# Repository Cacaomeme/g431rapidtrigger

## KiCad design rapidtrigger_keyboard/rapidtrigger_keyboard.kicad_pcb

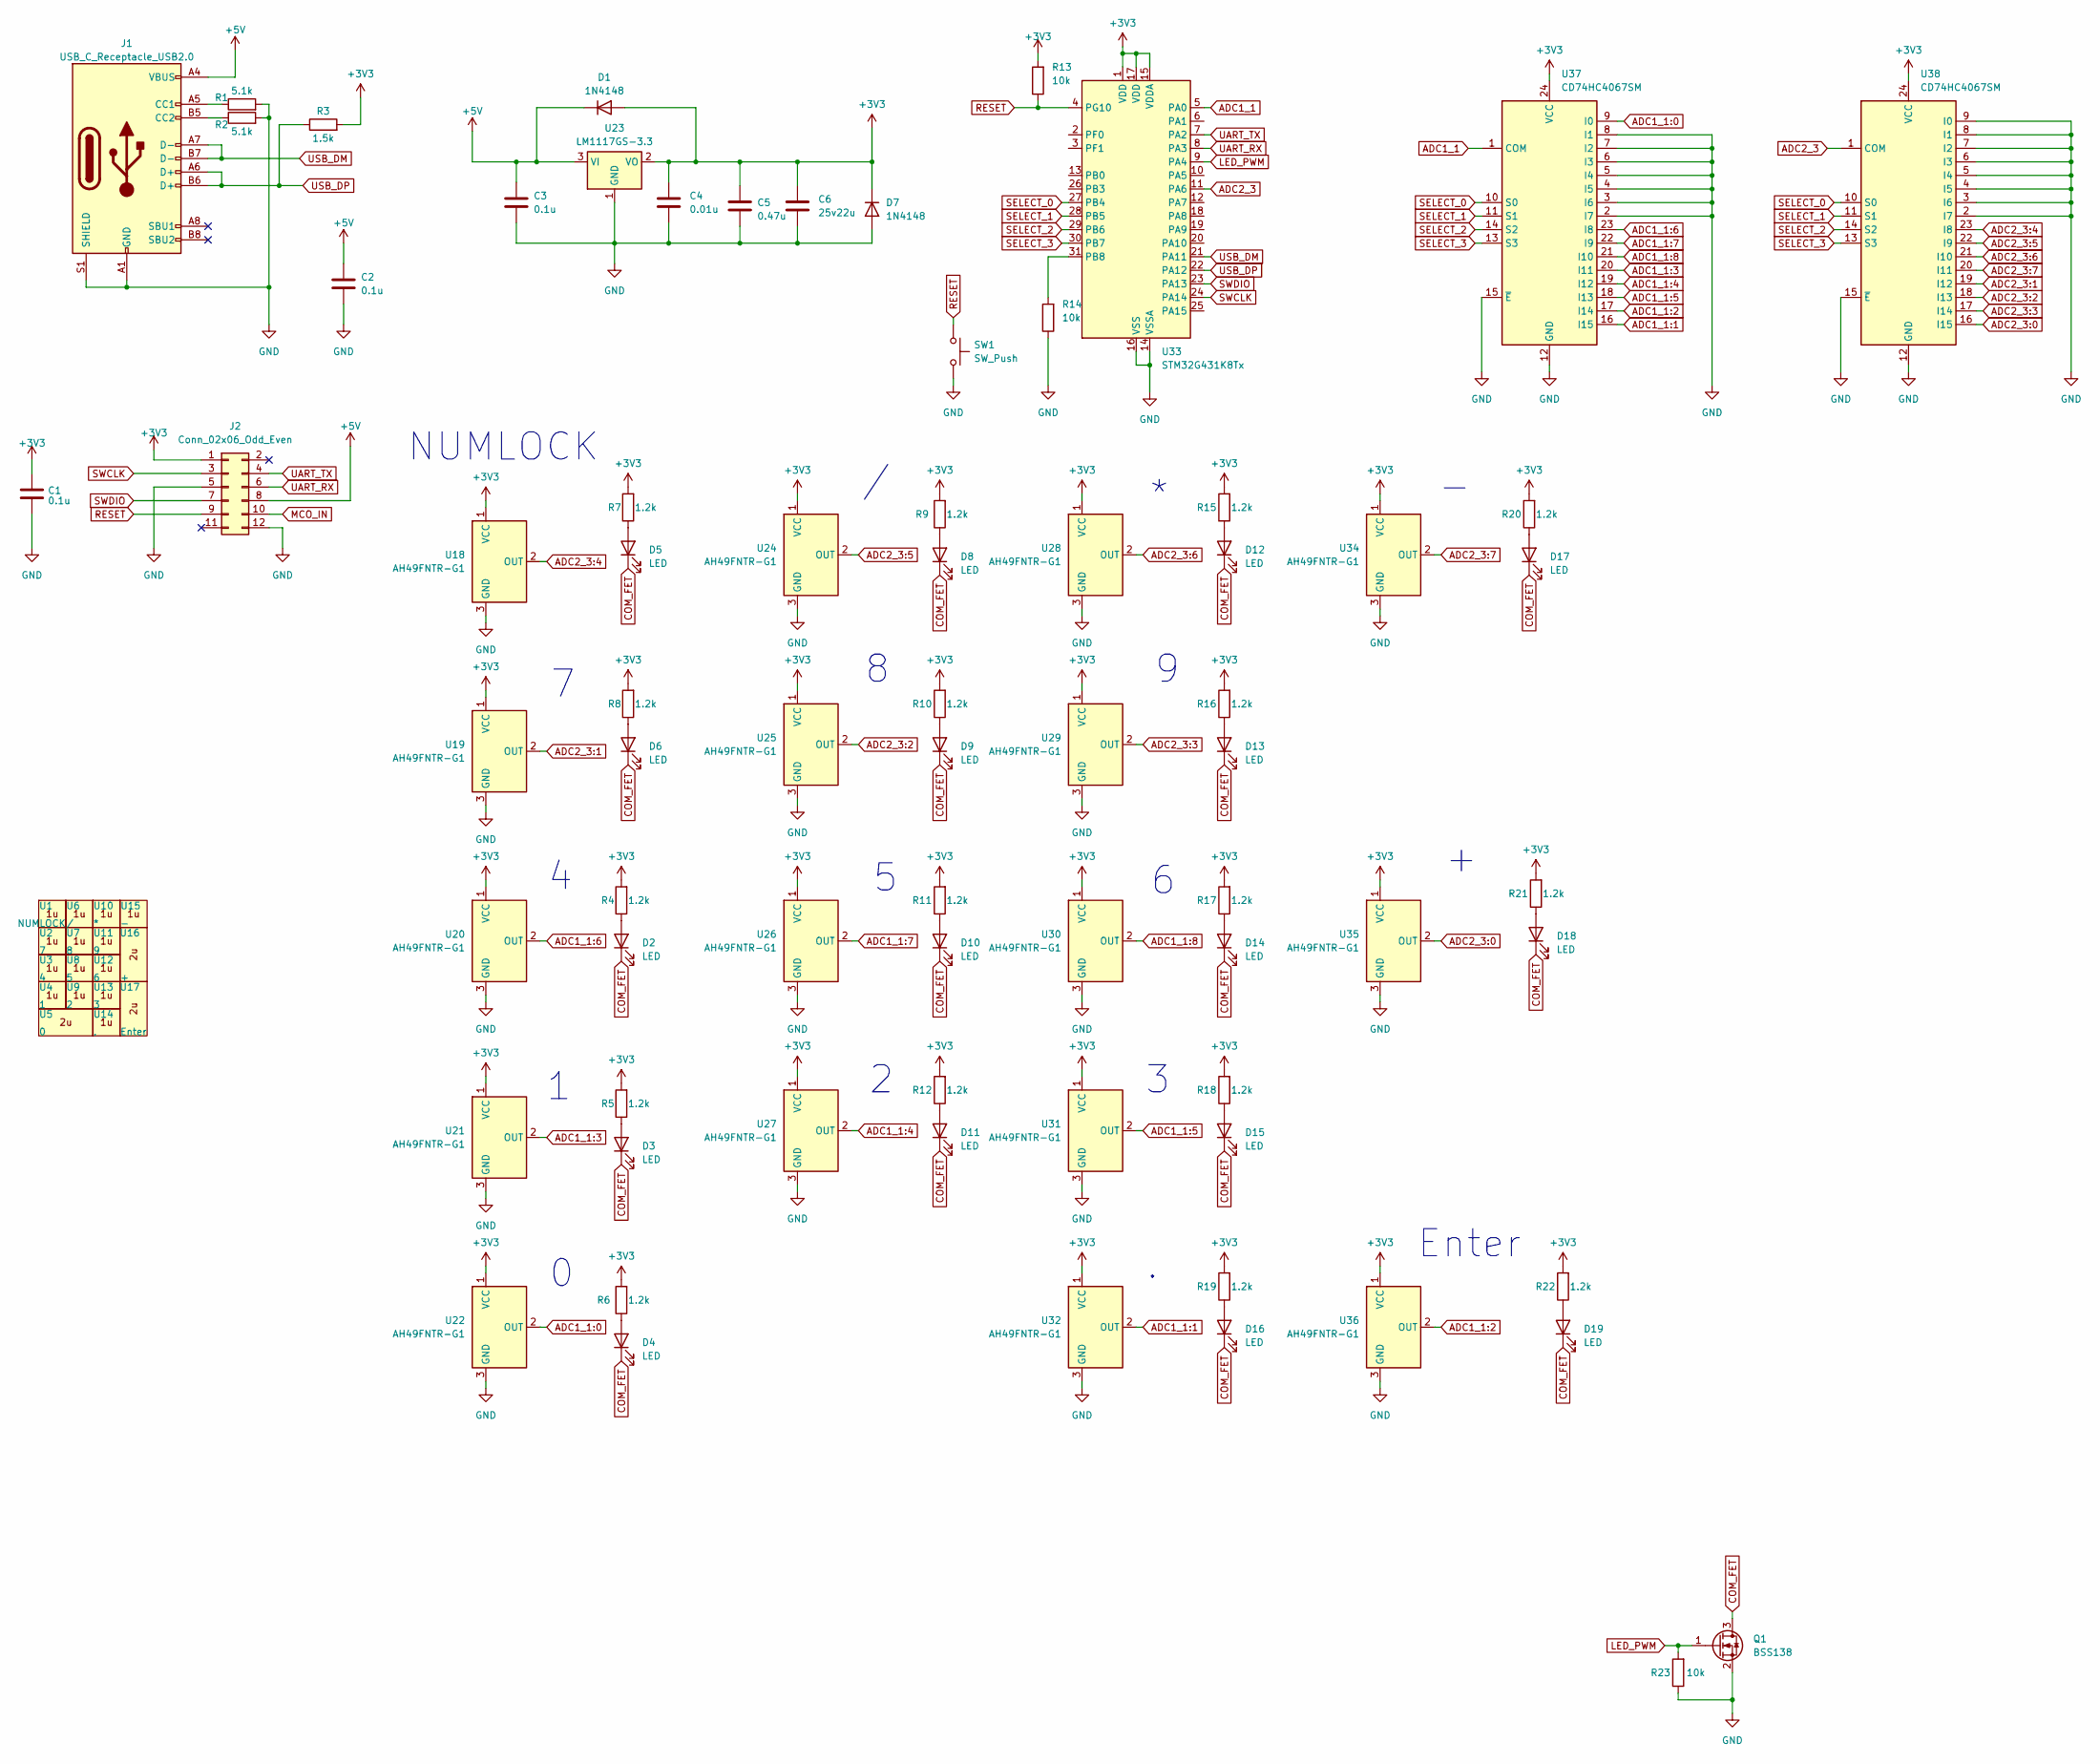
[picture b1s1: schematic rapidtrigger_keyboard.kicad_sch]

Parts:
C1, C2, C3: 0.1u; C_0603_1608Metric_Pad1.08x0.95mm_HandSolder
C4: 0.01u; C_0603_1608Metric_Pad1.08x0.95mm_HandSolder
C5: 0.47u; C_0603_1608Metric_Pad1.08x0.95mm_HandSolder
C6: 25v22u; C_0805_2012Metric_Pad1.18x1.45mm_HandSolder
D1, D7: 1N4148; D_SOD-123
D2, D3, D4, D5, D6, D8, D9, D10, D11, D12, D13, D14, D15, D16, D17, D18, D19: LED; LED_0603_1608Metric_Pad1.05x0.95mm_HandSolder
J1: USB_C_Receptacle_USB2.0; USB_C_Receptacle_HRO_TYPE-C-31-M-12
J2: Conn_02x06_Odd_Even; PinSocket_2x06_P2.54mm_Horizontal
Q1: BSS138; SOT-23
R1, R2: 5.1k; R_0603_1608Metric_Pad0.98x0.95mm_HandSolder
R3: 1.5k; R_0603_1608Metric_Pad0.98x0.95mm_HandSolder
R4, R5, R6, R7, R8, R9, R10, R11, R12, R15, R16, R17, R18, R19, R20, R21, R22: 1.2k; R_0603_1608Metric_Pad0.98x0.95mm_HandSolder
R13, R14, R23: 10k; R_0603_1608Metric_Pad0.98x0.95mm_HandSolder
SW1: SW_Push; SW_PUSH_6mm
U1: NUMLOCK; KS-20_1u
U2: 7; KS-20_1u
U3: 4; KS-20_1u
U4: 1; KS-20_1u
U5: 0; KS-20_2u
U6: /; KS-20_1u
U7: 8; KS-20_1u
U8: 5; KS-20_1u
U9: 2; KS-20_1u
U10: *; KS-20_1u
U11: 9; KS-20_1u
U12: 6; KS-20_1u
U13: 3; KS-20_1u
U14: .; KS-20_1u
U15: -; KS-20_1u
U16: +; KS-20_2u
U17: Enter; KS-20_2u
U18, U19, U20, U21, U22, U24, U25, U26, U27, U28, U29, U30, U31, U32, U34, U35, U36: AH49FNTR-G1; SOT-23
U23: LM1117GS-3.3; SOT-223-3_TabPin2
U33: STM32G431K8Tx; LQFP-32_7x7mm_P0.8mm
U37, U38: CD74HC4067SM; SSOP-24_5.3x8.2mm_P0.65mm

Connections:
+3V3: C1.1, C4.1, C5.1, C6.1, D1.2 (A), D7.1 (K), J2.1, R3.2, R4.2, R5.2, R6.2, R7.2, R8.2, R9.2, R10.2, R11.2, R12.2, R13.2, R15.2, R16.2, R17.2, R18.2, R19.2, R20.2, R21.2, R22.2, U18.1 (VCC), U19.1 (VCC), U20.1 (VCC), U21.1 (VCC), U22.1 (VCC), U23.2 (VO), U24.1 (VCC), U25.1 (VCC), U26.1 (VCC), U27.1 (VCC), U28.1 (VCC), U29.1 (VCC), U30.1 (VCC), U31.1 (VCC), U32.1 (VCC), U33.1 (VDD), U33.15 (VDDA), U33.17 (VDD), U34.1 (VCC), U35.1 (VCC), U36.1 (VCC), U37.24 (VCC), U38.24 (VCC)
+5V: C2.1, C3.1, D1.1 (K), J1.A4 (VBUS), J1.A9 (VBUS), J1.B4 (VBUS), J1.B9 (VBUS), J2.8, U23.3 (VI)
ADC1_1: U33.5 (PA0), U37.1 (COM)
ADC1_1:0: U22.2 (OUT), U37.9 (I0)
ADC1_1:1: U32.2 (OUT), U37.16 (I15)
ADC1_1:2: U36.2 (OUT), U37.17 (I14)
ADC1_1:3: U21.2 (OUT), U37.20 (I11)
ADC1_1:4: U27.2 (OUT), U37.19 (I12)
ADC1_1:5: U31.2 (OUT), U37.18 (I13)
ADC1_1:6: U20.2 (OUT), U37.23 (I8)
ADC1_1:7: U26.2 (OUT), U37.22 (I9)
ADC1_1:8: U30.2 (OUT), U37.21 (I10)
ADC2_3: U33.11 (PA6), U38.1 (COM)
ADC2_3:0: U35.2 (OUT), U38.16 (I15)
ADC2_3:1: U19.2 (OUT), U38.19 (I12)
ADC2_3:2: U25.2 (OUT), U38.18 (I13)
ADC2_3:3: U29.2 (OUT), U38.17 (I14)
ADC2_3:4: U18.2 (OUT), U38.23 (I8)
ADC2_3:5: U24.2 (OUT), U38.22 (I9)
ADC2_3:6: U28.2 (OUT), U38.21 (I10)
ADC2_3:7: U34.2 (OUT), U38.20 (I11)
COM_FET: D2.1 (K), D3.1 (K), D4.1 (K), D5.1 (K), D6.1 (K), D8.1 (K), D9.1 (K), D10.1 (K), D11.1 (K), D12.1 (K), D13.1 (K), D14.1 (K), D15.1 (K), D16.1 (K), D17.1 (K), D18.1 (K), D19.1 (K), Q1.3 (D)
GND: C1.2, C2.2, C3.2, C4.2, C5.2, C6.2, D7.2 (A), J1.A1 (GND), J1.A12 (GND), J1.B1 (GND), J1.B12 (GND), J1.S1 (SHIELD), J2.5, J2.12, Q1.2 (S), R1.2, R2.2, R14.1, R23.1, SW1.2, U18.3 (GND), U19.3 (GND), U20.3 (GND), U21.3 (GND), U22.3 (GND), U23.1 (GND), U24.3 (GND), U25.3 (GND), U26.3 (GND), U27.3 (GND), U28.3 (GND), U29.3 (GND), U30.3 (GND), U31.3 (GND), U32.3 (GND), U33.14 (VSSA), U33.16 (VSS), U33.32 (VSS), U34.3 (GND), U35.3 (GND), U36.3 (GND), U37.2 (I7), U37.3 (I6), U37.4 (I5), U37.5 (I4), U37.6 (I3), U37.7 (I2), U37.8 (I1), U37.12 (GND), U37.15 (~E), U38.2 (I7), U38.3 (I6), U38.4 (I5), U38.5 (I4), U38.6 (I3), U38.7 (I2), U38.8 (I1), U38.9 (I0), U38.12 (GND), U38.15 (~E)
LED_PWM: Q1.1 (G), R23.2, U33.9 (PA4)
MCO_IN: J2.10
unnamed: D2.2 (A), R4.1
unnamed: D3.2 (A), R5.1
unnamed: D4.2 (A), R6.1
unnamed: D5.2 (A), R7.1
unnamed: D6.2 (A), R8.1
unnamed: D8.2 (A), R9.1
unnamed: D9.2 (A), R10.1
unnamed: D10.2 (A), R11.1
unnamed: D11.2 (A), R12.1
unnamed: D12.2 (A), R15.1
unnamed: D13.2 (A), R16.1
unnamed: D14.2 (A), R17.1
unnamed: D15.2 (A), R18.1
unnamed: D16.2 (A), R19.1
unnamed: D17.2 (A), R20.1
unnamed: D18.2 (A), R21.1
unnamed: D19.2 (A), R22.1
unnamed: J1.A5 (CC1), R1.1
unnamed: J1.B5 (CC2), R2.1
unnamed: R14.2, U33.31 (PB8)
RESET: J2.9, R13.1, SW1.1, U33.4 (PG10)
SELECT_0: U33.27 (PB4), U37.10 (S0), U38.10 (S0)
SELECT_1: U33.28 (PB5), U37.11 (S1), U38.11 (S1)
SELECT_2: U33.29 (PB6), U37.14 (S2), U38.14 (S2)
SELECT_3: U33.30 (PB7), U37.13 (S3), U38.13 (S3)
SWCLK: J2.3, U33.24 (PA14)
SWDIO: J2.7, U33.23 (PA13)
UART_RX: J2.6, U33.8 (PA3)
UART_TX: J2.4, U33.7 (PA2)
USB_DM: J1.A7 (D-), J1.B7 (D-), U33.21 (PA11)
USB_DP: J1.A6 (D+), J1.B6 (D+), R3.1, U33.22 (PA12)

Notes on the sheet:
NUMLOCK
Enter

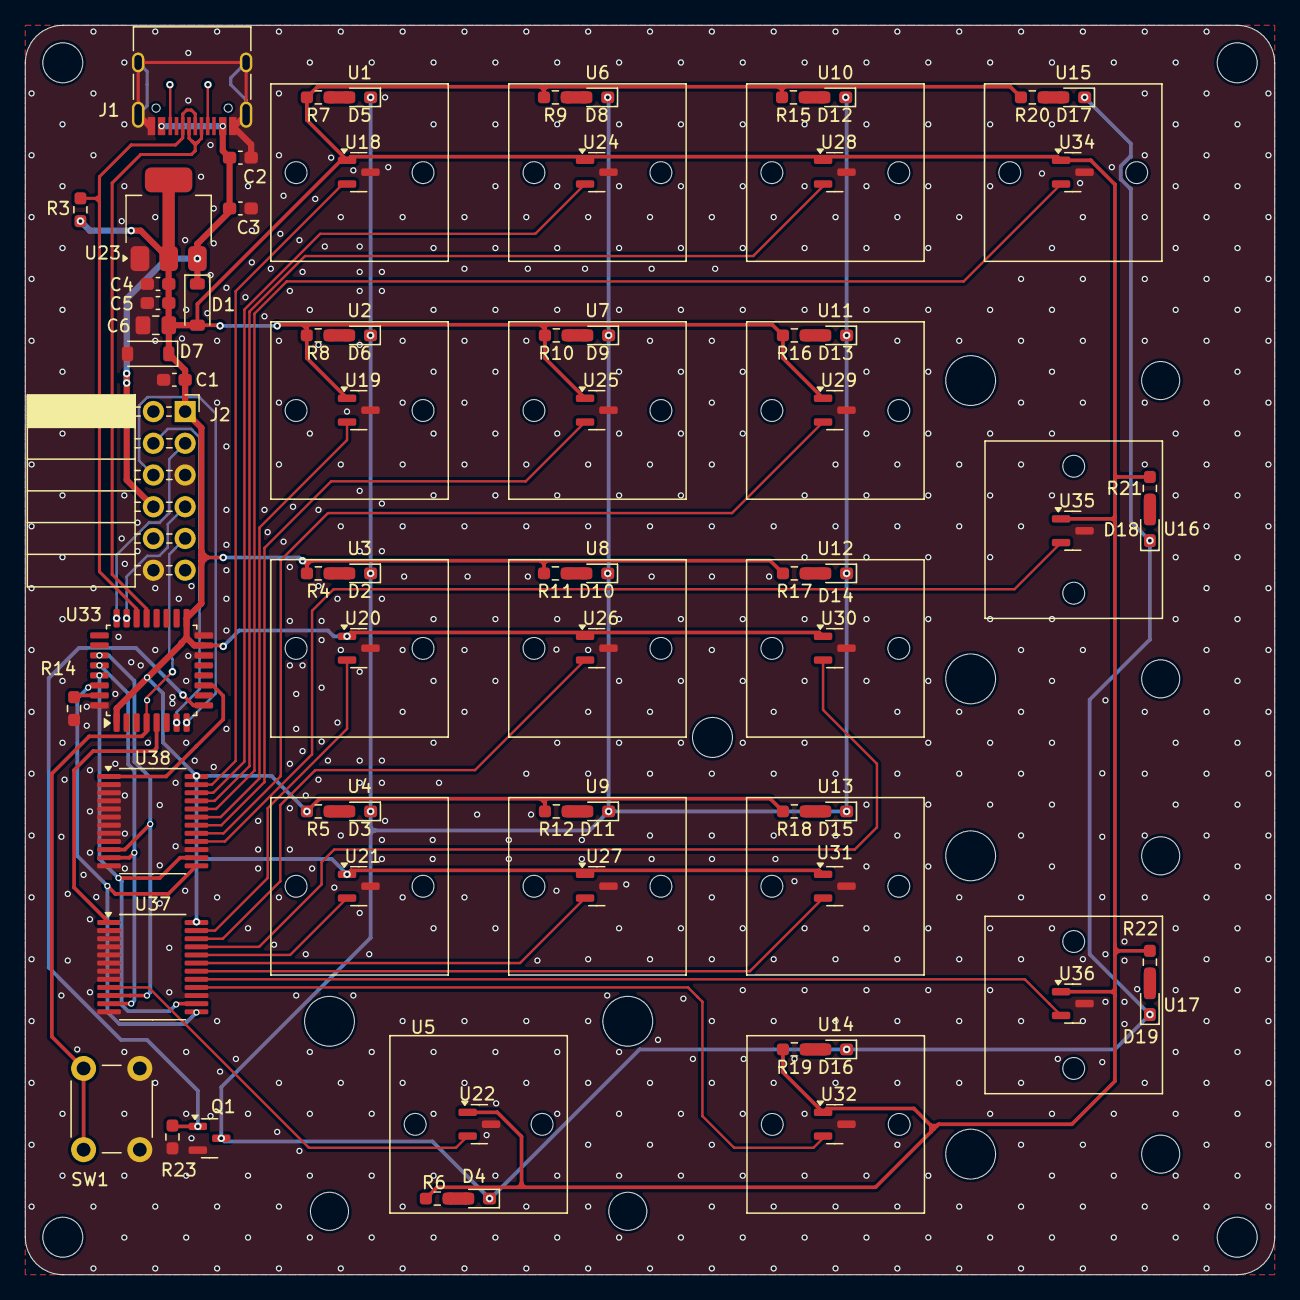
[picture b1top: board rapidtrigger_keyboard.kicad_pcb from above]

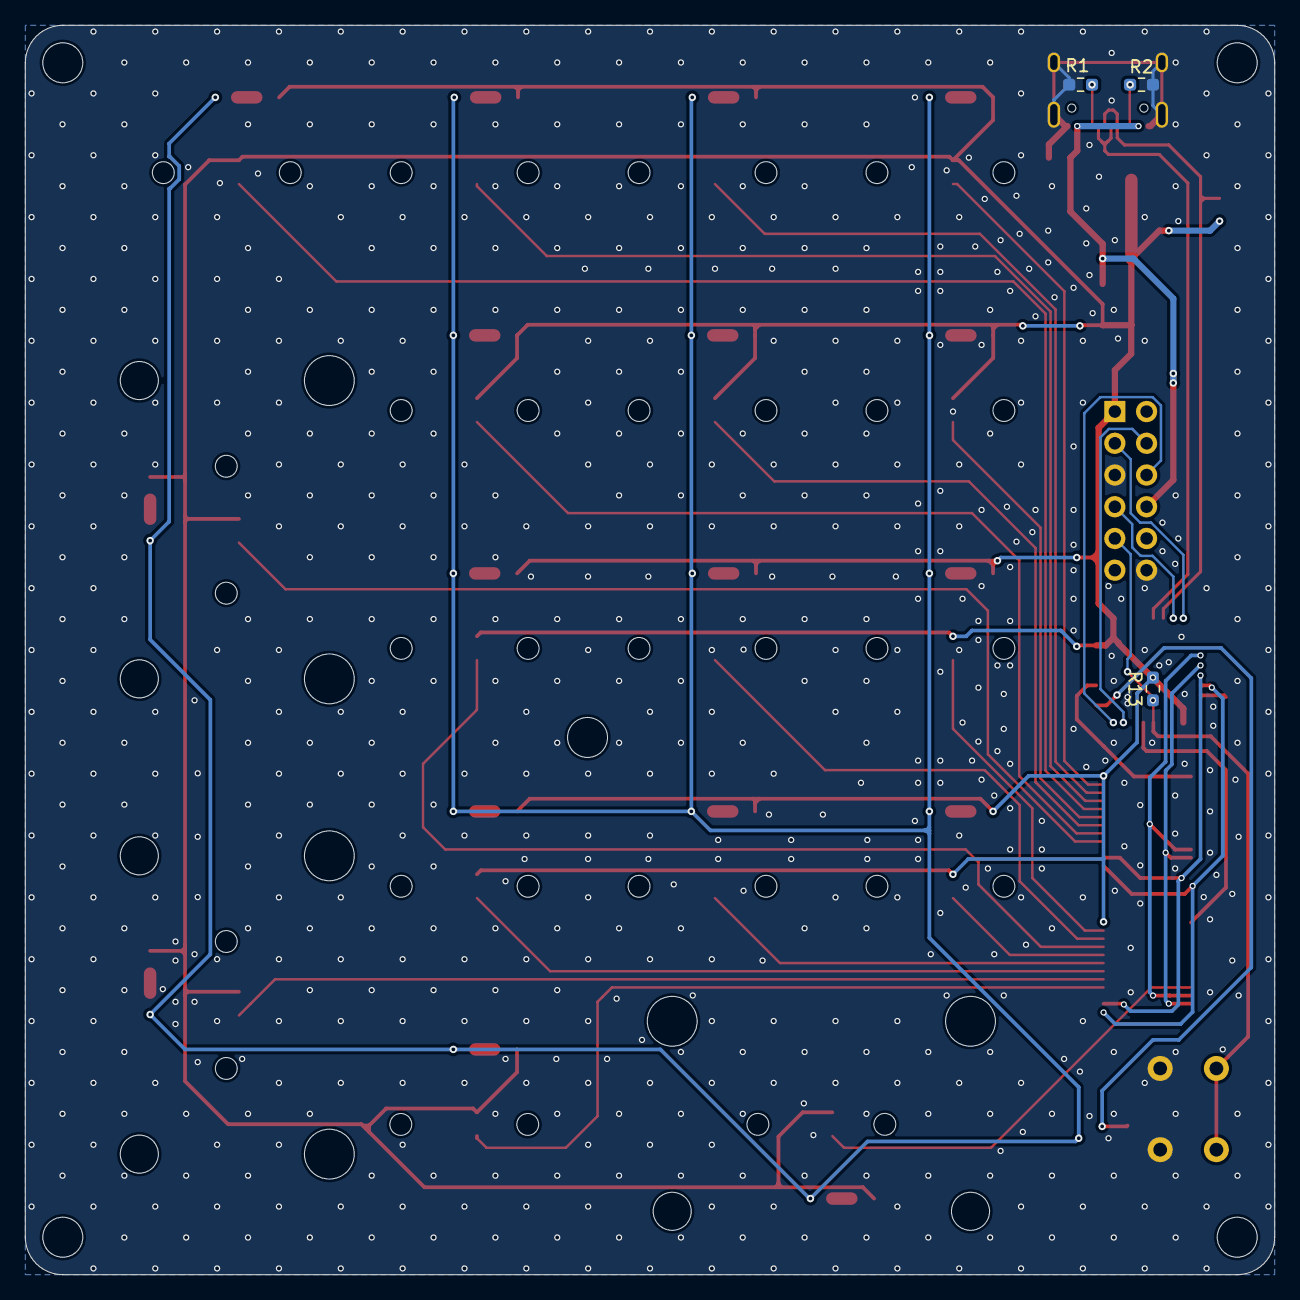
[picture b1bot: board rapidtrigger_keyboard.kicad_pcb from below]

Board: 2 copper layers, 100.0 x 100.0 mm, 90 parts (3 on the bottom side), 55 nets.

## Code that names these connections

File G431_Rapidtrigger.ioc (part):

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Mcu.Name=STM32G431K(6-8-B)Tx
Mcu.Package=LQFP32
Mcu.UserName=STM32G431KBTx
PA0.Mode=IN1-Single-Ended
PA0.Signal=ADC1_IN1
PA1.Mode=IN2-Single-Ended
PA1.Signal=ADC1_IN2
PA11.Mode=Device
PA11.Signal=USB_DM
PA12.Mode=Device
PA12.Signal=USB_DP
PA13.GPIOParameters=GPIO_Label
PA13.GPIO_Label=T_SWDIO
PA13.Mode=Serial_Wire
PA13.Signal=SYS_JTMS-SWDIO
PA14.GPIOParameters=GPIO_Label
PA14.GPIO_Label=T_SWCLK
PA14.Mode=Serial_Wire
PA14.Signal=SYS_JTCK-SWCLK
PA2.GPIOParameters=GPIO_Label
PA2.GPIO_Label=USART2_TX [ST-LINKV3E_VCP_RX]
PA2.Mode=Asynchronous
PA2.Signal=USART2_TX
PA3.GPIOParameters=GPIO_Label
PA3.GPIO_Label=USART2_RX [ST-LINKV3E_VCP_TX]
PA3.Mode=Asynchronous
PA3.Signal=USART2_RX
PA4.Signal=S_TIM3_CH2
PA6.Mode=IN3-Single-Ended
PA6.Signal=ADC2_IN3
PA7.Mode=IN4-Single-Ended
PA7.Signal=ADC2_IN4
PB0.Mode=IN15-Single-Ended
PB0.Signal=ADC1_IN15
PB3.GPIOParameters=GPIO_Label
PB3.GPIO_Label=T_SWO
PB3.Signal=SYS_JTDO-SWO
PB4.Signal=GPIO_Output
PB5.Signal=GPIO_Output
PB6.Signal=GPIO_Output
PB7.Signal=GPIO_Output
PB8-BOOT0.Signal=GPIO_Output
PF0-OSC_IN.Mode=IN10-Single-Ended
PF0-OSC_IN.Signal=ADC1_IN10
PF1-OSC_OUT.Mode=IN10-Single-Ended
PF1-OSC_OUT.Signal=ADC2_IN10
RCC.HSE_VALUE=8000000
RCC.SYSCLKFreq_VALUE=170000000
RCC.SYSCLKSource=RCC_SYSCLKSOURCE_PLLCLK
board=NUCLEO-G431KB
boardIOC=true
